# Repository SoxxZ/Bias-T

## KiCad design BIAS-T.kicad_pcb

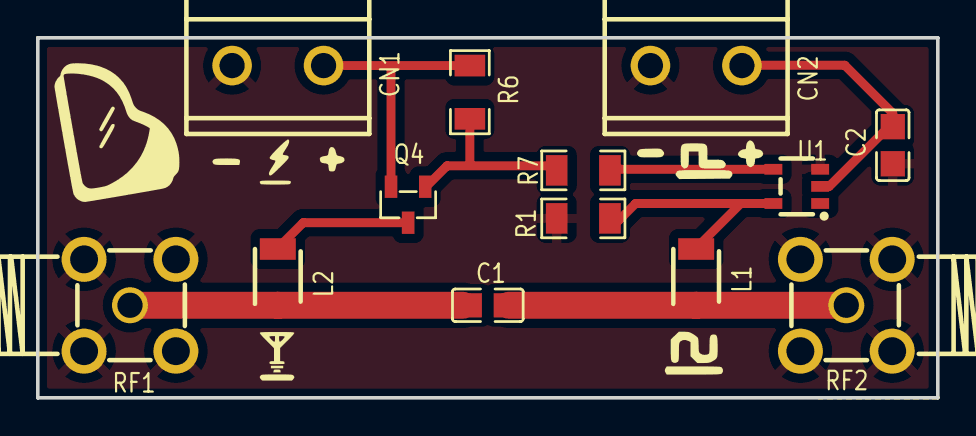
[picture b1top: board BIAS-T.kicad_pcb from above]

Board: 2 copper layers, 50.0 x 20.0 mm, 18 parts (0 on the bottom side), 8 nets.

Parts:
 : LOGO
 #2,  #3,  #4,  #5: LOGO
C1: 100pF; C0805
C2: 100nF; C0805
CN1, CN2: JL127-50002G01; CONN-TH_2P-P5.08_JL127-50002G01
L1, L2: 1.8 uH; IND-SMD_L3.2-W2.5
Q4: AO3401A; SOT-23-3_L2.9-W1.3-P1.90-LS2.4-BR
R1, R6: 10K; R1206
R7: 1K; R1206
RF1, RF2: HJ-SMA429; SMA-TH_HJ-SMA429
U1: SN74LVC1G04DBVR_C434067; SOT-23-5_L3.0-W1.7-P0.95-LS2.8-BR

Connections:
C1_1: C1.1, L2.2, RF1.1
CN2_1: C2.2, CN2.1, L1.1, R1.2, U1.1, U1.2, U1.5
GND: C2.1, CN1.2, CN2.2, R1.1, RF1.2, RF1.3, RF1.4, RF1.5, RF2.2, RF2.3, RF2.4, RF2.5, U1.3
Q4_2: CN1.1, Q4.2, R6.1
Q4_3: L2.1, Q4.3
R7_1: R7.1, U1.4
R7_2: Q4.1, R6.2, R7.2
RF2_1: C1.2, L1.2, RF2.1

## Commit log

2022-10-21 add files
